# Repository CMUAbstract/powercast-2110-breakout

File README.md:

# Breakout board for Powercast P2110 module to 0.100'' pins

Useful for connecting a [Powercast
P2110](http://www.powercastco.com/products/powerharvester-receivers/) module to
a breadboard or to 0.100'' headers for connecting jumper wires.

This repository contains Eagle design files for the schematic and board layout.

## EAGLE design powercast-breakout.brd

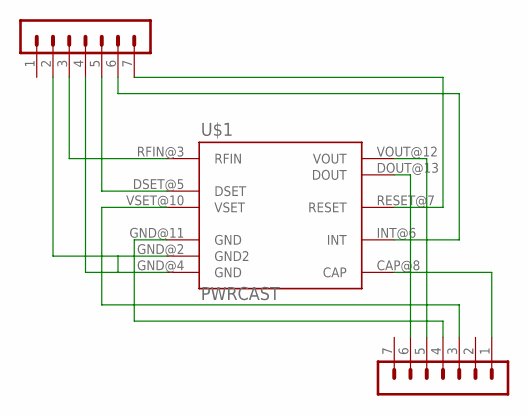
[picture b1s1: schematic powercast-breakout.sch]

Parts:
S: MA07-1OCTAGON-NS; MA07-1-SMALL-NOSILK
SV2: MA07-1OCTAGON-NS; MA07-1-SMALL-NOSILK
U$1: PWRCAST; POWERCASTRCVMOD

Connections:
GND: S.2, S.4, U$1.GND@2 (GND2), U$1.GND@4 (GND)
unnamed: S.3, U$1.RFIN@3 (RFIN)
unnamed: S.5, U$1.DSET@5 (DSET)
unnamed: S.7, U$1.RESET@7 (RESET)
unnamed: S.6, U$1.INT@6 (INT)
unnamed: SV2.1, U$1.CAP@8 (CAP)
unnamed: SV2.6, U$1.DOUT@13 (DOUT)
unnamed: SV2.5, U$1.VOUT@12 (VOUT)
unnamed: SV2.4, U$1.GND@11 (GND)
unnamed: SV2.3, U$1.VSET@10 (VSET)

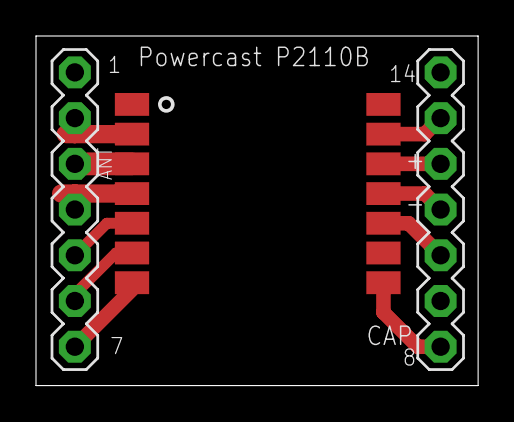
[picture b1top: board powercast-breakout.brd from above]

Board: 2 copper layers, 24.6 x 19.4 mm, 3 parts (0 on the bottom side), 10 nets.

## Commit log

2018-03-13 powercast breakout design files
